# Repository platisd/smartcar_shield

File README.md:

# Smartcar shield

A versatile and easy to use vehicle platform for hobby-grade projects

* [Description](#description)
* [Hardware](#hardware)
  * [Platform](#platform)
  * [Shield](#shield)
  * [Emulator](#emulator)
* [Software](#software)
* [Reference platforms](#reference-platforms)
  * [Smartcar platform (default setup)](#smartcar-platform-default-setup)
  * [Smartcar shield](#smartcar-shield-1)
  * [Supported sensors](#supported-sensors)
* [How to get started](#how-to-get-started)
* [Dependencies](#dependencies)
* [Project documentation](#project-documentation)
* [License](#license)

## Description
This repository, includes everything necessary to set up a Smartcar platform.
The Smartcar, is a vehicular educational platform, which enables the user to develop
various robotic applications in an affordable, pedagogic and easy way. It is intended
for persons with basic programming knowledge and little to no experience of electronics,
mechanics or robotics. More experienced users, should also find this approach convenient,
due to its open source nature, high level API and object oriented design.

## Hardware
Despite the software being hardware-agnostic, historically, development has been based on specific
hardware. Initially, the **Smartcar shield** was used on top of an Arduino, using cheap car kits.
This setup will be referred to as `shield` or `v1`.

Since the winter of 2019, a new platform was developed from scratch, using the WiFi and Bluetooth
enabled ESP32 as the vehicle's "brain". This setup will be referred to as `platform` or `v2` and
will be considered the default one from now on. It offers greater robustness and many more
possibilities, as it offers out-of-the-box connectivity.

### Platform

The Smartcar platform is a complete hardware solution for your hobby-grade, connected vehicle project.
It is comprised of the chassis, made out of printed circuit boards, stacked on each other and an
ESP32 development board that drives the motors, controls the sensors and communicates with the
world via WiFi and Bluetooth.

There are 4 motors with directional odometers which enable not only to determine how much the
wheels have moved but also the direction they spin. It is equipped with a GY-50 gyroscope module
(based on the L3G4200D sensor) to provide heading information and sockets to optionally connect
4 `VL45L0X` LIDAR sensors to provide distance measurements. It is powered up by 8 AA batteries
and you can find the boards' source files in [extras/eagle/smartcar_platform](/extras/eagle/smartcar_shield).

### Shield

The Smartcar shield is an open hardware PCB, that is effortlessly stacked on top of an Arduino. It
includes an L293D H-bridge chip, that drives the motors, screw terminals to connect the motors
and a battery to them and a GY-50 gyroscope module (based on the L3G4200D sensor).
In [extras/eagle/smartcar_shield](/extras/eagle/smartcar_shield) you can find the
design files for the board, in a modifiable form, using free software. There are
also the options, to order it as-is, from either USA or China based manufacturers.

The Smartcar shield, facilitates efficient cable management, helps to preserve space
and is as small as possible, in order to keep the manufacturing price low. Additionally,
the components necessary to assemble it, are widely available over the Internet. Furthermore,
you can find 2D CAD drawings of the Smartcar chassis in various formats, at
[/extras/cad/2D](extras/cad/2D) which you can freely use in order to fabricate your own,
e.g. with a milling machine or a laser cutter.

### Emulator

[SMCE](https://github.com/ItJustWorksTM/smce-gd/) is the digital twin of the Smartcar platform
along with a cool and customisable 3D world for your rover to roam in.<br>
The core concept is that you write Arduino code that runs on both the real hardware as well as
the virtual environment.
This way, the need to have exclusive and frequent access to the car can be either alleviated
or drastically decreased.
The emulator allows limiting the unavoidable engagement with the physical car, to the point a
team of developers may develop their features on the emulator and only access the real hardware
to verify them.

## Software
The software, is the Smartcar shield Arduino library. It sports a high level API, meant to
enable its users to perform tasks easily with relatively few lines of code. It intends to
hide implementation details or low level hardware operations. The library, handles
the various components (i.e. the vehicle and the various sensors) as objects, therefore
enabling trivial control over the car's functions. The various operations exposed by the API,
are thoroughly explained in [API Documentation](https://platisd.github.io/smartcar_shield/).
You can find examples on how to use the library, in [/examples](/examples).

The library is versatile and is independent from the shield or specific hardware.
Particularly, its most important feature is that it supports multiple ways of steering and
throttling with different types of motors. Moreover, it is possible to steer the vehicle by
rotating the wheels on each side at a different speed, like a tank as well as by using a
servo motor. Another option is to use a brushed DC motor for steering, a setup that is very
common in cheap RC cars. Additionally, apart of the default brushed DC motors that are
connected to the Smartcar shield, you can also use an electronic speed controller (ESC)
in order to drive (throttle) the vehicle, using the very same library.

If the Smartcar shield library is installed through the Library Manager of Arduino IDE, as
recommended, the user will receive a notification in their IDE, when new versions are released
making updates particularly easy, without the need to use GitHub or git.

## Reference platforms

### Smartcar platform (default setup)

* 1 x [Modules board (rev.2)](https://www.pcbway.com/project/shareproject/Smartcar___Modules_board_rev_2.html)
* 1 x [Motor board (rev. 0)](https://www.pcbway.com/project/shareproject/Smartcar___Motors_board.html)
* 4 x [Brushed motors](https://www.aliexpress.com/item/32872592243.html) (530rpm @ 12V)
* 2 x [TXS0108E TTL level shifters](https://www.aliexpress.com/item/32472491036.html)
* 1 x DOIT ESP32 devkit v1 (30 GPIO pins)
* 1 x [TB6612FNG dual motor driver (Sparkfun)](https://www.sparkfun.com/products/14451)
* 4 x M6 (30mm) screws
* 4 x M6 nuts
* 16 x M3 (10mm) screws
* 16 x M3 nuts
* 2 x [HSP 02052 Front Bumper](https://www.aliexpress.com/item/32753903115.html)
* 10 x 6pin 2.54 pitch female pin headers
* 2 x 15pin 2.54 pitch female pin headers
* 1 x GY-50 gyroscope
* 4 x [8pin 2.54 pitch long male pin headers](https://www.aliexpress.com/item/32911455899.html) (30mm long)
* 4 x 8pin 2.54 pitch female pin headers
* 3 x 10KOhm resistors
* 8 x [AA battery holders](https://www.electrokit.com/produkt/batterihallare-1xaa-pcb/)
* 1 x [DD40AJSA adjustable buck converter](https://www.aliexpress.com/item/32816584868.html)
* 1 x [SPDT switch](https://www.tme.eu/en/details/5ms1s102am2qe/slide-switches/)
* 4 x [VL45L0x ToF distance sensors](https://www.aliexpress.com/item/32828144370.html) (optional)
  * 4 x 4pin 2.54 angled headers to mount the sensors vertically

### Smartcar shield

 * Smartcar chassis
 * [Smartcar shield PCB](extras/eagle/smartcar_shield)
 * L293D H-bridge
 * GY-50 gyroscope module
 * Two odometers (speed encoders) ([[1]](http://www.aliexpress.com/item/5pcs-IR-Infrared-Slotted-Optical-Speed-Measuring-Sensor-Optocoupler-Module-For-Motor-Test-For-Arduino-PIC/32465670452.html)
 and [[2]](http://www.aliexpress.com/item/HC-020K-Double-Speed-Measuring-Sensor-Module-with-Photoelectric-Encoders-Kit-top/32453020060.html)
 will suit commercially available chassis.
 [[3]](http://www.aliexpress.com/item/Correlation-photoelectric-sensor-lot-Infrared-correlation-count-sensor-module/2038553959.html)
 require some slight modifications)
 * Male & female pin headers (optionally get stackable Arduino headers too)
 * Five 2-pin screw terminals
 * Pin jumper
 * DIP16 socket
 * 0.1uF capacitors (2)
 * 100uF capacitor
 * 9V or 12V battery pack (do not use a single 9V battery)

### Supported sensors
 * Distance sensors
    * Ultrasonic
      * HC-SR04
      * SRF08
    * Infrared
      * SHARP GP2D120
      * SHARP GP2Y0A02
      * SHARP GP2Y0A21
 * Gyroscopes
   * GY-50 (L3G4200D)
 * Odometers
   * Directional (4+ pins)
   * Non-directional (3-pins)

## How to get started
 * Assemble the vehicle
 * [Install the library](https://www.ardu-badge.com/Smartcar%20shield)
 * [Connect the motors appropriately](examples/Car/shieldMotorsTest/shieldMotorsTest.ino) (if using the shield)
 * [Getting started with the Smartcar Platform](https://www.hackster.io/platisd/getting-started-with-the-smartcar-platform-1648ad)

## Dependencies
All dependencies should be downloaded automatically by the Arduino IDE's library manager.

- [Wire library](http://arduino.cc/en/reference/Wire)
- [Servo library](https://www.arduino.cc/en/reference/servo)
- [ESP32Servo](https://github.com/madhephaestus/ESP32Servo)

## Project documentation
* [API Documentation](https://platisd.github.io/smartcar_shield/)
* [The Smartcar platform](http://plat.is/smartcar)
* [Wiki](https://github.com/platisd/smartcar_shield/wiki)
* [Turning software engineers into Makers](https://platis.solutions/blog/2016/06/17/turning-software-engineers-into-makers/)

## License
MIT

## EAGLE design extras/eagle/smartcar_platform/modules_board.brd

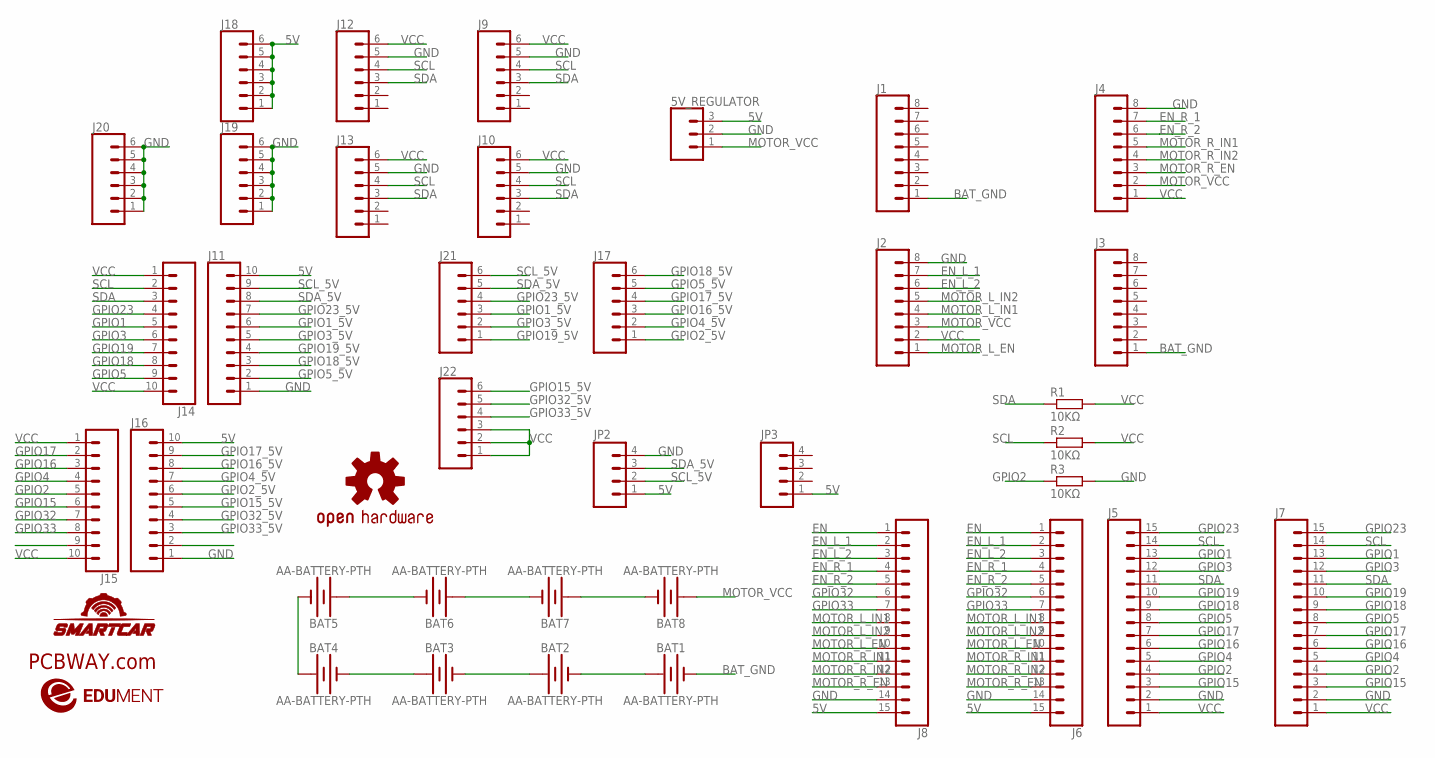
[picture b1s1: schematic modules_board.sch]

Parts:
5V_REGULATOR: CONN_03LOCK; 1X03_LOCK
BAT1, BAT2, BAT3, BAT4, BAT5, BAT6, BAT7, BAT8: AA-BATTERY-PTH; AA-PCB-BATTERY
J1, J2, J3, J4: CONN_08NO_SILK_FEMALE_PTH; 1X08_NO_SILK
J5, J6: CONN_15LOCK_LONGPADS; 1X15_LOCK_LONGPADS
J7, J8: CONN_15LOCK_NO_SILK; 1X15_LOCK_NO_SILK
J9, J10, J12, J13, J17, J18, J19, J20, J21, J22: CONN_06LOCK; 1X06_LOCK
J11, J14, J15, J16: CONN_10"; 1X10
JP2, JP3: M04NO_SILK_ALL_ROUND; 1X04_NO_SILK_ALL_ROUND
LOGO1: OSHW-LOGOL; OSHW-LOGO-L
R1, R2, R3: 10KΩ; 0207/12
SMRTCR1: SMARTCAR_LOGOMEDIUM; SMARTCAR_LOGO_MEDIUM
U$1: PCBWAY_LOGO
U$2: EDUMENT_LOGOLARGE; EDUMENT_LOGO_LARGE

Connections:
5V: 5V_REGULATOR.3, J6.15, J8.15, J11.10, J16.10, J18.1, J18.2, J18.3, J18.4, J18.5, J18.6, JP2.1, JP3.1
BAT_GND: BAT1.NEG (-), J1.1, J3.1
EN: J6.1, J8.1
EN_L_1: J2.7, J6.2, J8.2
EN_L_2: J2.6, J6.3, J8.3
EN_R_1: J4.7, J6.4, J8.4
EN_R_2: J4.6, J6.5, J8.5
GND: 5V_REGULATOR.2, J2.8, J4.8, J5.2, J6.14, J7.2, J8.14, J9.5, J10.5, J11.1, J12.5, J13.5, J16.1, J19.1, J19.2, J19.3, J19.4, J19.5, J19.6, J20.1, J20.2, J20.3, J20.4, J20.5, J20.6, JP2.4, R3.2
GPIO1: J5.13, J7.13, J14.5
GPIO1_5V: J11.6, J21.3
GPIO2: J5.4, J7.4, J15.5, R3.1
GPIO2_5V: J16.6, J17.1
GPIO3: J5.12, J7.12, J14.6
GPIO3_5V: J11.5, J21.2
GPIO4: J5.5, J7.5, J15.4
GPIO4_5V: J16.7, J17.2
GPIO5: J5.8, J7.8, J14.9
GPIO5_5V: J11.2, J17.5
GPIO15: J5.3, J7.3, J15.6
GPIO15_5V: J16.5, J22.6
GPIO16: J5.6, J7.6, J15.3
GPIO16_5V: J16.8, J17.3
GPIO17: J5.7, J7.7, J15.2
GPIO17_5V: J16.9, J17.4
GPIO18: J5.9, J7.9, J14.8
GPIO18_5V: J11.3, J17.6
GPIO19: J5.10, J7.10, J14.7
GPIO19_5V: J11.4, J21.1
GPIO23: J5.15, J7.15, J14.4
GPIO23_5V: J11.7, J21.4
GPIO32: J6.6, J8.6, J15.7
GPIO32_5V: J16.4, J22.5
GPIO33: J6.7, J8.7, J15.8
GPIO33_5V: J16.3, J22.4
MOTOR_L_EN: J2.1, J6.10, J8.10
MOTOR_L_IN1: J2.4, J6.8, J8.8
MOTOR_L_IN2: J2.5, J6.9, J8.9
MOTOR_R_EN: J4.3, J6.13, J8.13
MOTOR_R_IN1: J4.5, J6.11, J8.11
MOTOR_R_IN2: J4.4, J6.12, J8.12
MOTOR_VCC: 5V_REGULATOR.1, BAT8.POS (+), J2.3, J4.2
unnamed: BAT2.POS (+), BAT3.NEG (-)
unnamed: BAT1.POS (+), BAT2.NEG (-)
unnamed: BAT3.POS (+), BAT4.NEG (-)
unnamed: BAT4.POS (+), BAT5.NEG (-)
unnamed: BAT5.POS (+), BAT6.NEG (-)
unnamed: BAT6.POS (+), BAT7.NEG (-)
unnamed: BAT7.POS (+), BAT8.NEG (-)
SCL: J5.14, J7.14, J9.4, J10.4, J12.4, J13.4, J14.2, R2.1
SCL_5V: J11.9, J21.6, JP2.2
SDA: J5.11, J7.11, J9.3, J10.3, J12.3, J13.3, J14.3, R1.1
SDA_5V: J11.8, J21.5, JP2.3
VCC: J2.2, J4.1, J5.1, J7.1, J9.6, J10.6, J12.6, J13.6, J14.1, J14.10, J15.1, J15.10, J22.1, J22.2, J22.3, R1.2, R2.2

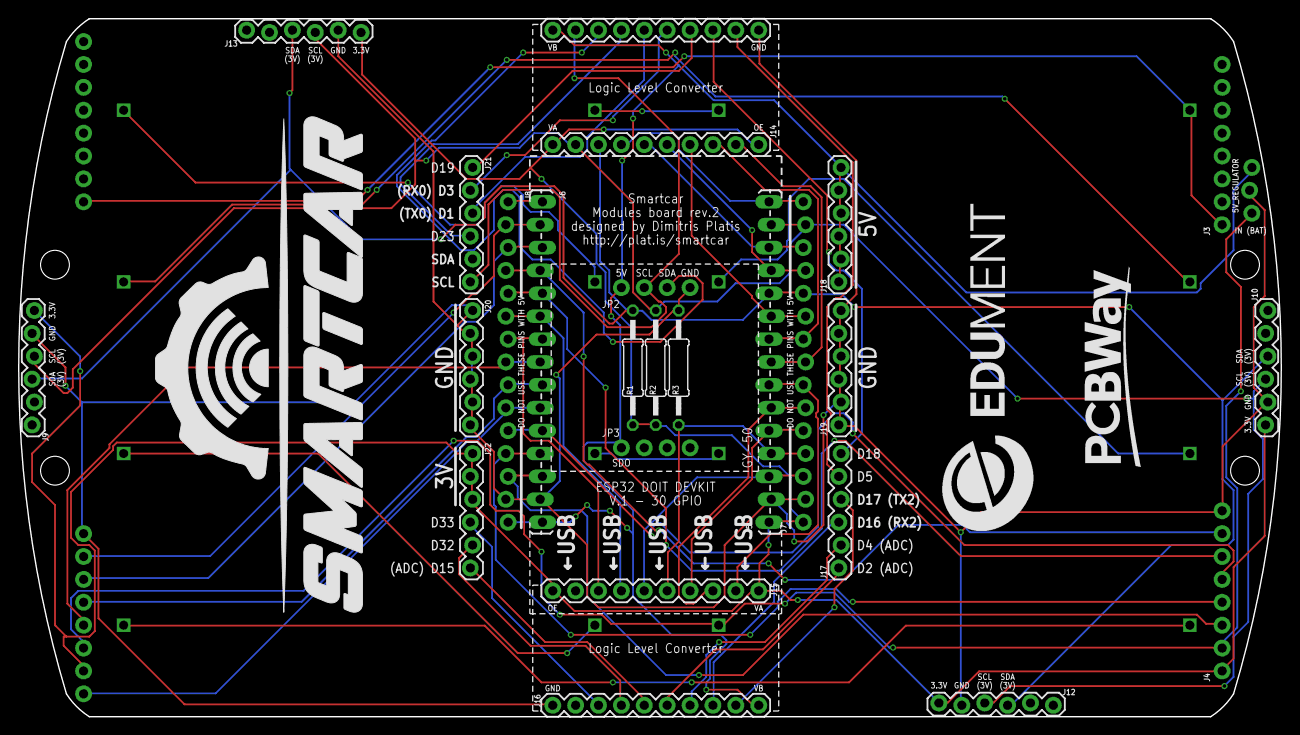
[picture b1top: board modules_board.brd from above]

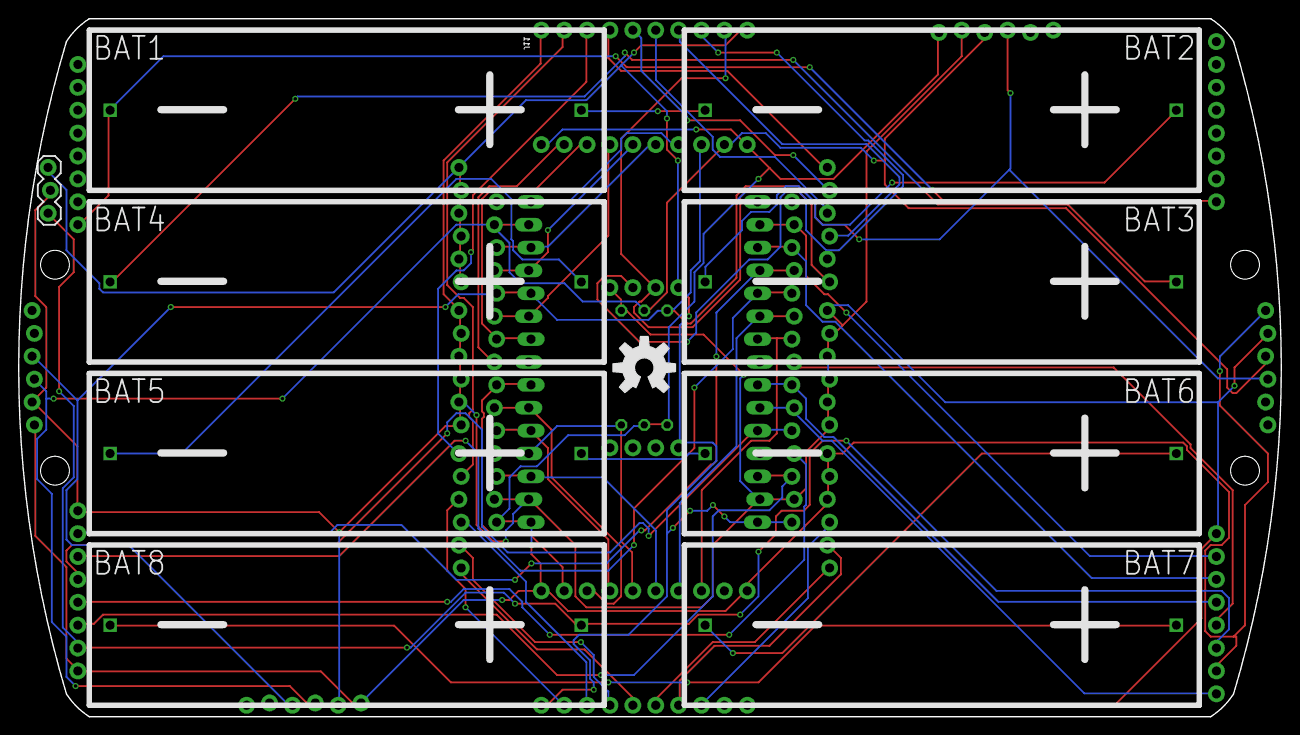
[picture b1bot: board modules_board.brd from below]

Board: 2 copper layers, 140.1 x 77.5 mm, 40 parts (10 on the bottom side), 53 nets.

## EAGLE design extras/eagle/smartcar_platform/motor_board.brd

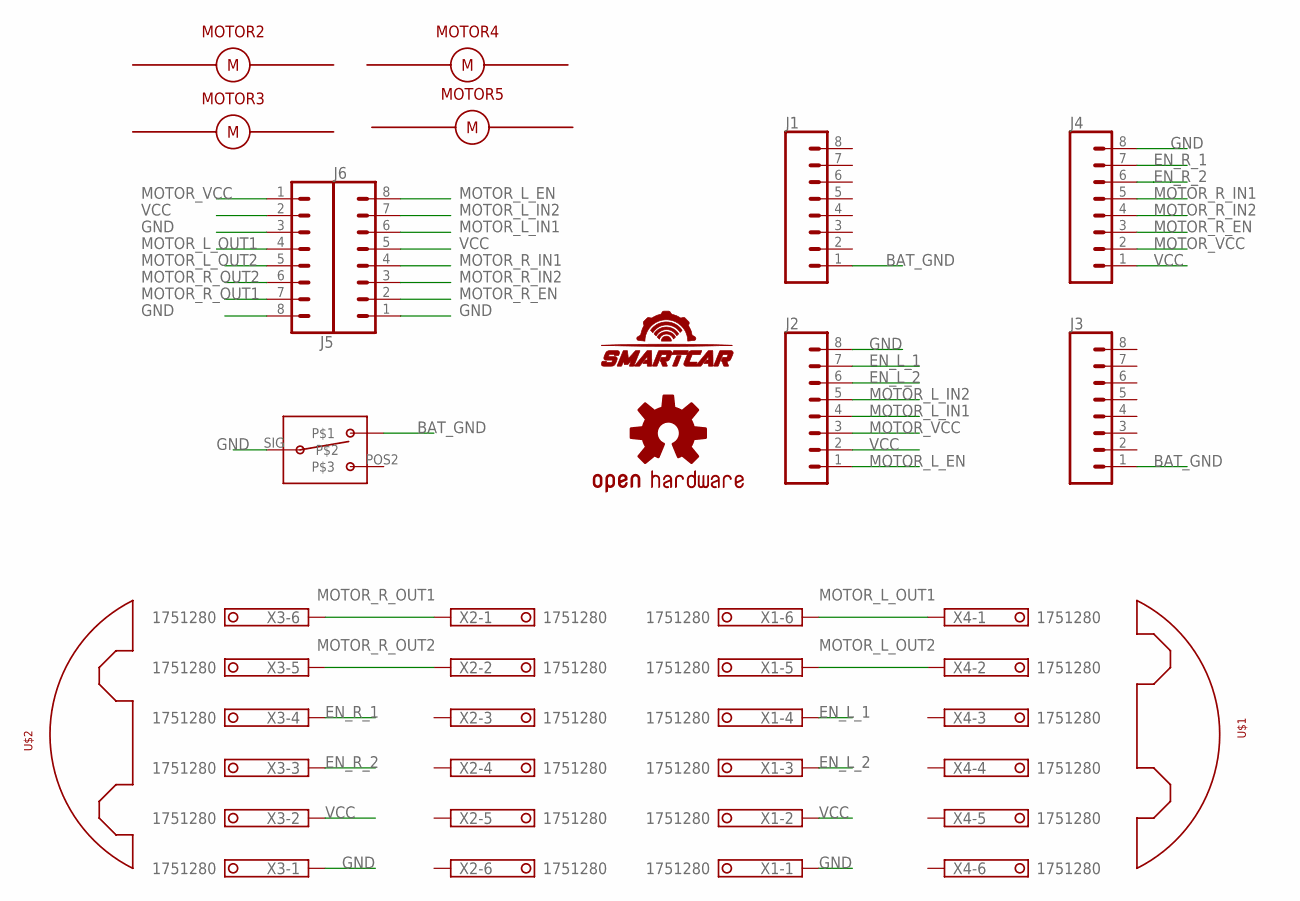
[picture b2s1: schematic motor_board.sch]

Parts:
J1, J2, J3, J4: CONN_08NO_SILK_FEMALE_PTH; 1X08_NO_SILK
J5, J6: CONN_08"; 1X08
LOGO1: OSHW-LOGOL; OSHW-LOGO-L
MOTOR2, MOTOR3, MOTOR4, MOTOR5: SMARTCAR_MOTOR; SMARTCAR_MOTOR_MOUNT_HOLES
SMRTCR1: SMARTCAR_LOGOMEDIUM; SMARTCAR_LOGO_MEDIUM
SW1: SPDT-HIGH-AMP-SWITCHPTH; SPDT-0.2-THICK-PINS
U$1, U$2: BUMPER_020522_SCREWS; BUMPER_2_SCREWS_NARROW
X1, X2, X3, X4: 1751280

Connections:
BAT_GND: J1.1, J3.1, SW1.POS1
EN_L_1: J2.7, X1.4
EN_L_2: J2.6, X1.3
EN_R_1: J4.7, X3.4
EN_R_2: J4.6, X3.3
GND: J2.8, J4.8, J5.3, J5.8, J6.1, SW1.SIG, X1.1, X3.1
MOTOR_L_EN: J2.1, J6.8
MOTOR_L_IN1: J2.4, J6.6
MOTOR_L_IN2: J2.5, J6.7
MOTOR_L_OUT1: J5.4, X1.6, X4.1
MOTOR_L_OUT2: J5.5, X1.5, X4.2
MOTOR_R_EN: J4.3, J6.2
MOTOR_R_IN1: J4.5, J6.4
MOTOR_R_IN2: J4.4, J6.3
MOTOR_R_OUT1: J5.7, X2.1, X3.6
MOTOR_R_OUT2: J5.6, X2.2, X3.5
MOTOR_VCC: J2.3, J4.2, J5.1
VCC: J2.2, J4.1, J5.2, J6.5, X1.2, X3.2

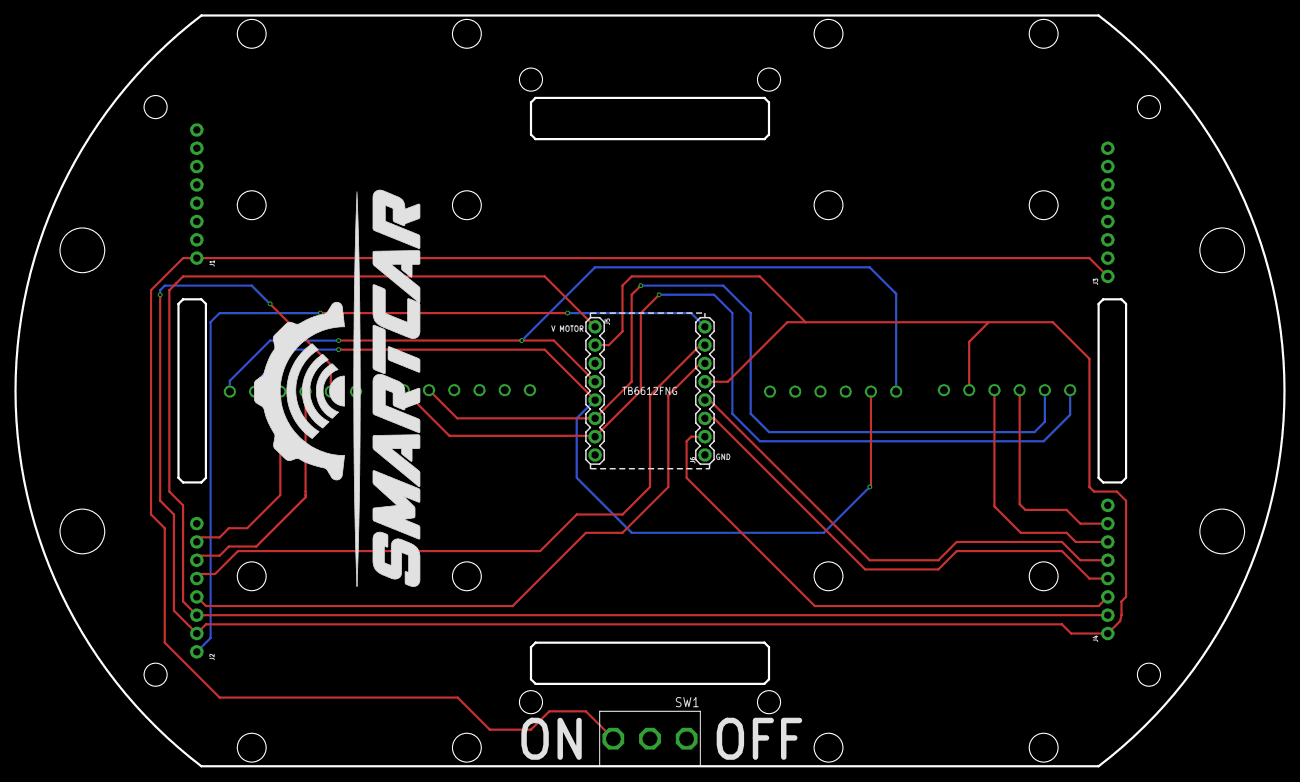
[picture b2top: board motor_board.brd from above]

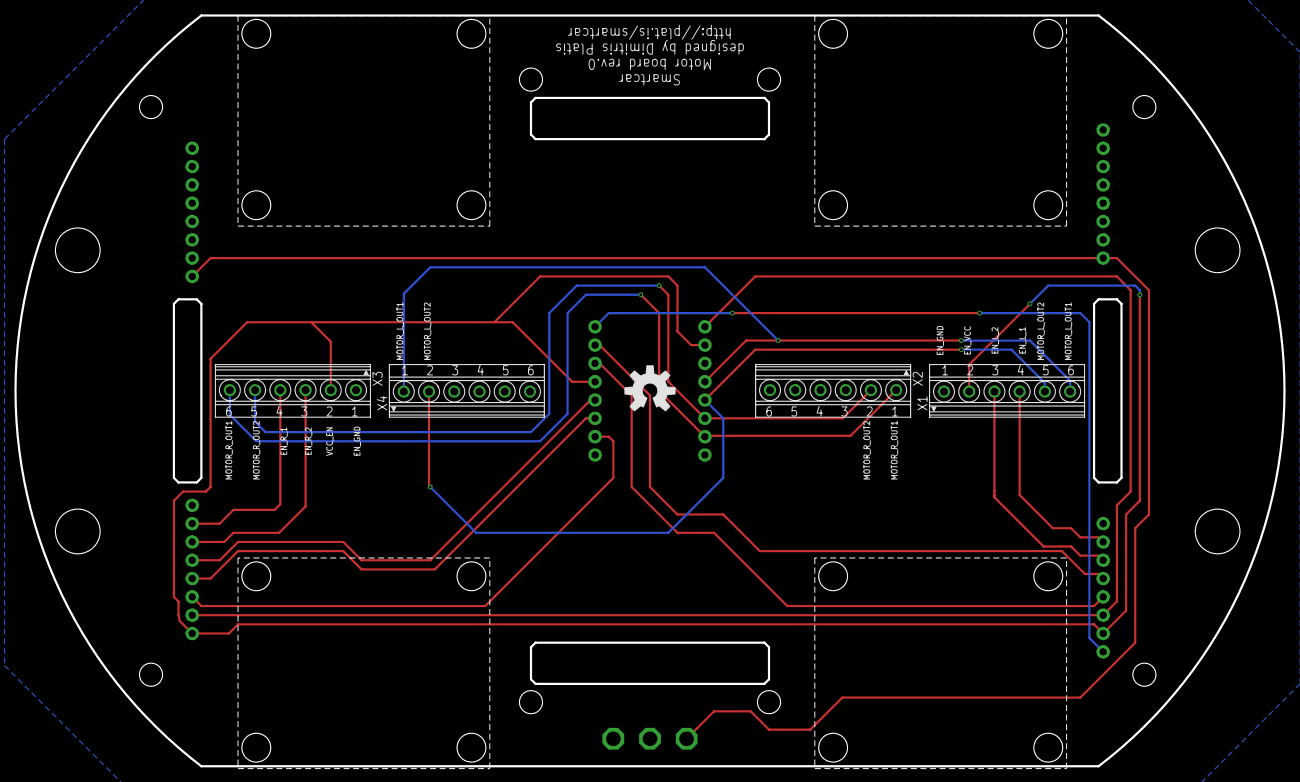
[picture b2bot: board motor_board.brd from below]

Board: 2 copper layers, 176.0 x 104.1 mm, 19 parts (9 on the bottom side), 18 nets.

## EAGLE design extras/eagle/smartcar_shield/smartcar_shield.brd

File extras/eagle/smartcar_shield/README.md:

# Smartcar shield CAD files

### Description
Here you can find the files necessary in order to edit or manufacture the Smartcar shield PCB. The files can be opened using CAD software, such as Eagle PCB that is free for personal use and KiCad, which is open source. The .sch file includes the logical schematic of the circuit, that is how the various components are connected to each other and the .brd file illustrates how they will be printed on the actual board.

All components that are needed for the board, are through-hole, for easy soldering. Finally, feel free to edit or redistribute the shield. Pull requests are always welcome.

### Order a PCB
If you do not want to bother with CAD softwareand just want to buy the PCBs for the shield, I have uploaded the necessary files in two popular services, [OSH-Park](https://oshpark.com/) (USA) and [PCBWay](https://www.pcbway.com/) (China), so they can be purchased with a few clicks.

**Note: I am not affiliated with either of these services, however I do receive a 10% commission in coupons from [PCBway](https://www.pcbway.com/) when you order the boards from them.**

* [PCBWay](https://www.pcbway.com/project/shareproject/SmartCar_Shield_rev__2.html) (rev. 2)
* [OSH-Park](https://oshpark.com/shared_projects/pCO3kBPB) (rev. 2)

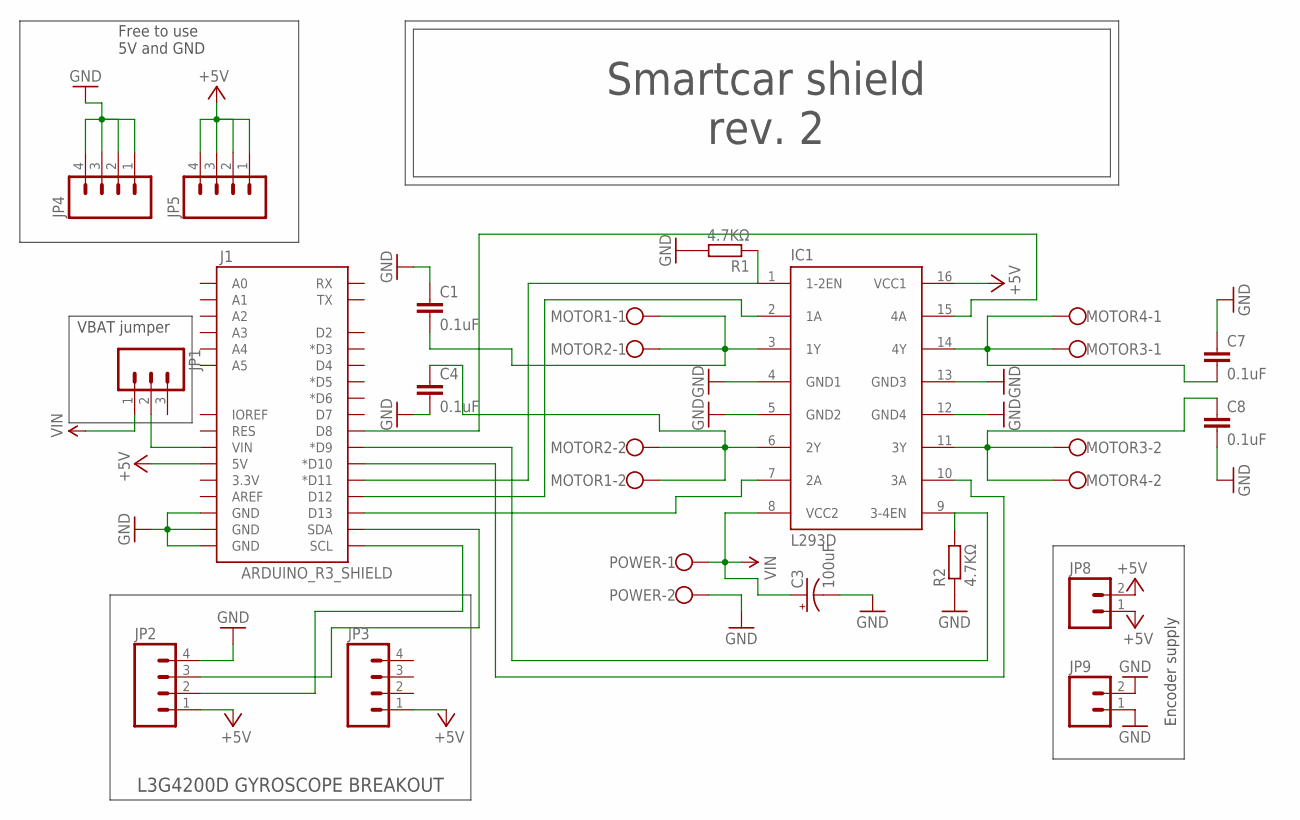
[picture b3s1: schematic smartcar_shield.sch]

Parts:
C1, C4, C7, C8: 0.1uF; CAP-PTH-SMALL-KIT
C3: 100uF; CPOL-RADIAL-10UF-25V
IC1: L293D; DIL16
J1: ARDUINO_R3_SHIELD; UNO_R3_SHIELD
JP1: M03PTH; 1X03
JP2, JP3, JP4, JP5: M04NO_SILK_ALL_ROUND; 1X04_NO_SILK_ALL_ROUND
JP8, JP9: M021X02_NO_SILK; 1X02_NO_SILK
MOTOR1, MOTOR2, MOTOR3, MOTOR4: W237-102
POWER: W237-102
R1, R2: 4.7KΩ; 0207/10

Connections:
12V: C3.1 (+), IC1.8 (VCC2), JP1.1, POWER.1
+5V: IC1.16 (VCC1), J1.5V, JP2.1, JP3.1, JP5.1, JP5.2, JP5.3, JP5.4, JP8.1, JP8.2
ENABLE1: IC1.1 (1-2EN), J1.D11 (*D11), R1.1
ENABLE2: IC1.9 (3-4EN), J1.D9 (*D9), R2.2
GND: C1.1, C3.2 (-), C4.2, C7.1, C8.2, IC1.4 (GND1), IC1.5 (GND2), IC1.12 (GND4), IC1.13 (GND3), J1.GND@0 (GND), J1.GND@1 (GND), J1.GND@2 (GND), JP2.4, JP4.1, JP4.2, JP4.3, JP4.4, JP9.1, JP9.2, POWER.2, R1.2, R2.1
MOTORA-1: IC1.2 (1A), J1.D12
MOTORA-2: IC1.7 (2A), J1.D13
MOTORA-OUT1: C1.2, IC1.3 (1Y), MOTOR1.1, MOTOR2.1
MOTORA-OUT2: C4.1, IC1.6 (2Y), MOTOR1.2, MOTOR2.2
MOTORB-1: IC1.15 (4A), J1.D8
MOTORB-2: IC1.10 (3A), J1.D10 (*D10)
MOTORB-OUT1: C7.2, IC1.14 (4Y), MOTOR3.1, MOTOR4.1
MOTORB-OUT2: C8.1, IC1.11 (3Y), MOTOR3.2, MOTOR4.2
unnamed: J1.SDA, JP2.3
SCL: J1.SCL, JP2.2
VIN: J1.VIN, JP1.2

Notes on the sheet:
Encoder supply
Free to use 5V and GND
VBAT jumper
Smartcar shield rev. 2
L3G4200D GYROSCOPE BREAKOUT

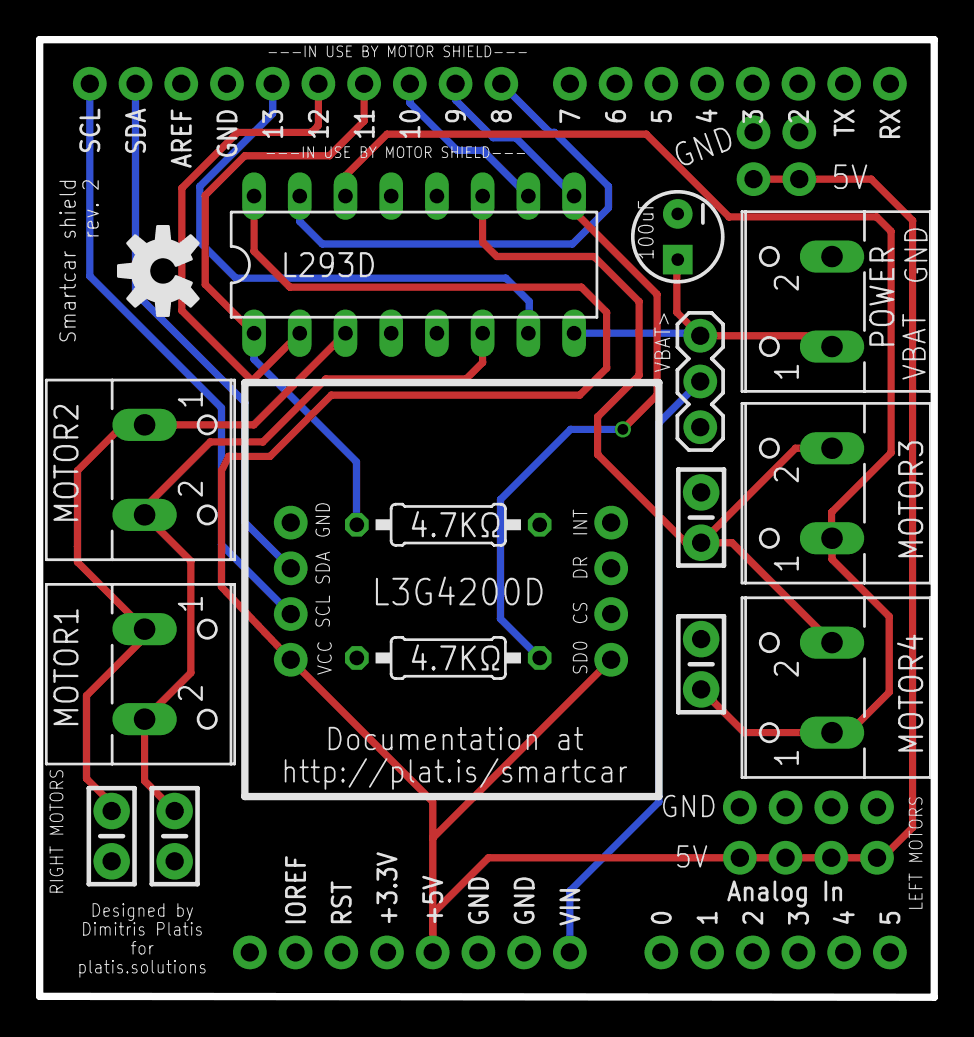
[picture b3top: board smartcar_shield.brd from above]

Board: 2 copper layers, 49.7 x 53.2 mm, 22 parts (0 on the bottom side), 16 nets.

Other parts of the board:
U$1: OSHW-LOGO-M

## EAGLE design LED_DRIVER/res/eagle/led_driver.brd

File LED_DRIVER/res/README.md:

# LED DRIVER
The LED driver board, is based on an ATTiny85 microcontroller and is used in order to drive the LEDs that can be found on the vehicle and particularly the direction indicators. In the [/res](res) folder, you can find the board's schema, how it looks like and also the Eagle files if you want to modify it or fabricate it yourself. Moreover, if you want just to reproduce the board, you can order it from [OSH Park](https://oshpark.com/shared_projects/Hk4up6hJ).

### Materials used
* 6 screw terminals ([Sparkfun](https://www.sparkfun.com/products/8432))
* 4 NPN transistors (BC547)
* 4 1.5KΩ resistors
* 1 ATtiny85-20PU microcontroller
* 1 socket 8 DIP (optional but strongly recommended)

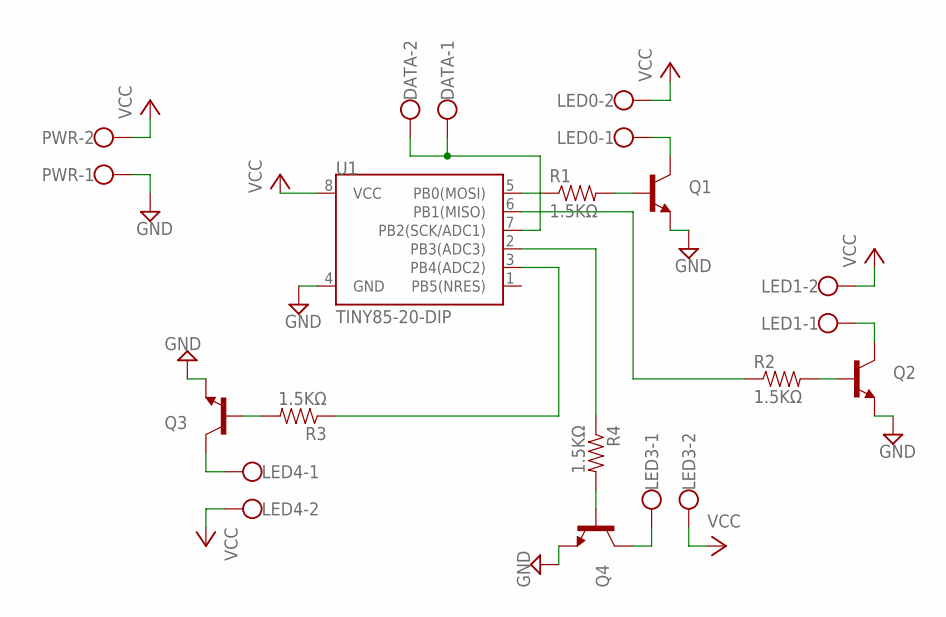
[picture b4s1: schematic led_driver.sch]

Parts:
DATA: W237-102
LED0, LED1, LED3, LED4: W237-102
PWR: W237-102
Q1, Q2, Q3, Q4: TRANSISTOR_NPNBC547; TO-92-AMMO
R1, R2, R4: 1.5ΚΩ; AXIAL-0.3
R3: 1.5KΩ; AXIAL-0.3
U1: TINY85-20-DIP; DIP08

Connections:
DATA-IN: DATA.1, DATA.2, U1.7 (PB2(SCK/ADC1))
GND: PWR.1, Q1.3 (E), Q2.3 (E), Q3.3 (E), Q4.3 (E), U1.4 (GND)
LED0: R1.P$1 (1), U1.5 (PB0(MOSI))
LED0-GND: LED0.1, Q1.1 (C)
LED1: R2.P$1 (1), U1.6 (PB1(MISO))
LED1-GND: LED1.1, Q2.1 (C)
LED3: R4.P$1 (1), U1.2 (PB3(ADC3))
LED3-GND: LED3.1, Q4.1 (C)
LED4: R3.P$1 (1), U1.3 (PB4(ADC2))
LED4-GND: LED4.1, Q3.1 (C)
unnamed: Q1.2 (B), R1.P$2 (2)
unnamed: Q2.2 (B), R2.P$2 (2)
unnamed: Q3.2 (B), R3.P$2 (2)
unnamed: Q4.2 (B), R4.P$2 (2)
VCC: LED0.2, LED1.2, LED3.2, LED4.2, PWR.2, U1.8 (VCC)

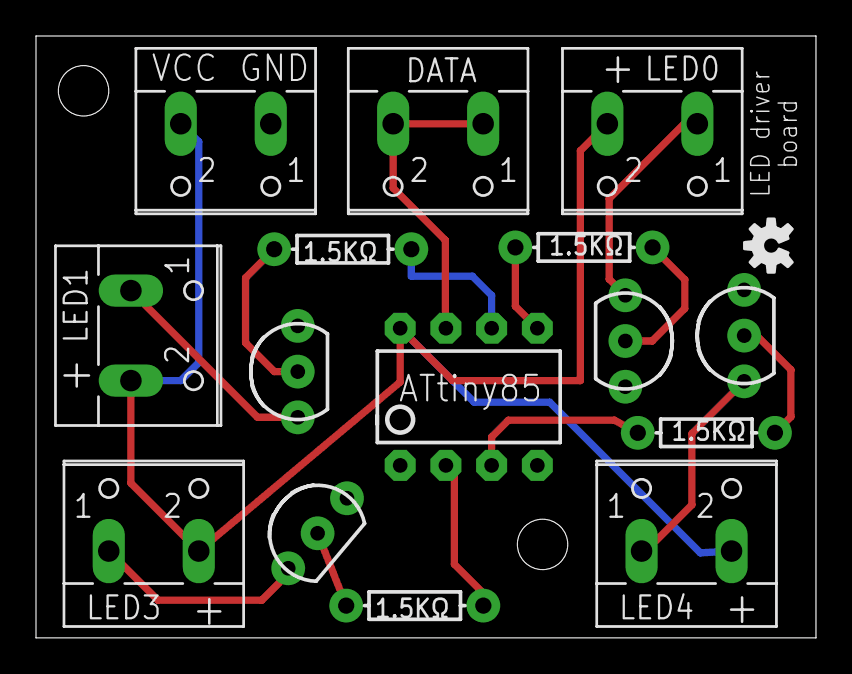
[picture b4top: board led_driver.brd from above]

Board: 2 copper layers, 43.3 x 33.4 mm, 16 parts (0 on the bottom side), 15 nets.

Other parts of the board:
U$1: OSHW-LOGO-S

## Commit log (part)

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2017-01-16 user to set the state the direction pin should be in when going forward
2017-01-16 Bumping version
    And also setting the default go speed back to what it was
2017-01-16 Revert "decreasing the maximum allowed speed for safety reasons"
    This reverts commit 70319889b9c457c7b791982763eb85e9415bb38e.
2017-01-16 new getDirection and Car class constructor For odometers that can provide the direction of movement and a Car with two motors attached to arbitrary pins
2017-01-16 decreasing the maximum allowed speed for safety reasons
2018-04-07 Remove i2c blocking loop
    Related to platisd/AndroidCar#1
2018-04-07 Fix wording
2018-05-14 solved method detection issue with @archico
2018-05-14 fixed method recognition for disableCruiseControl co-authored-by: Ilja Pavlov <guspavloil@student.gu.se>
2018-05-22 Bump library version with runaway fix
2018-07-23 Add version 5 structure
    Includes:
    * Folder structure
    * Interfaces and header files
2018-07-24 Add initial test structure
2018-07-24 Cache gtest sources
2018-07-24 Add coverage reports
2018-07-26 Rename Steering to Control
    Since we will be having the Steering-Throttling concepts
    later on, it's best to decouple these to avoid confusion
2018-07-26 Add Arduino runtime implementation
2018-07-26 Define DistanceSensor interface
2018-07-29 Add map and constrain functions
2018-09-30 Migrate SRF08 sensor class
2018-10-01 Add tests for SRF08 sensor
2018-10-01 Refactor SR04 sensor class
2018-10-12 Refactor SR04 class
2018-10-13 Refactor SHARP IR sensors
2018-10-14 Add new Odometer implementation
    TODO: Fix missing unit tests
2018-10-21 Test the Odometer constructor
2018-10-27 Rename orientation to heading
    For better representation of the business domain
2018-10-28 Refactor GY50 sensor (ex Gyroscope)
2018-10-30 Rename motor to motors
    Naming should be consistent with that of sensors
2018-10-31 Add brushless motor
2018-11-02 Use templatized map function instead of the Arduino one
2018-11-02 Add ServoMotor
2018-11-03 Add Ackerman and Differential controls
2018-11-03 Add utility function for tests and coverage
2018-11-04 Remove unused functions from runtime interface
2018-11-04 Test for not attached SHARP sensors
2018-11-04 Test reset() function of Directional odometer
2018-11-04 Rename odometer package
2018-11-04 Move directly-controlled odometers in separate folder
2018-11-04 Update tests and code after odometer renaming
2018-11-04 Adjust tests to directionless odometer naming
2018-11-04 Make SHARP sensor pin a constructor argument
    This will eliminate misuse and simplify the code
2018-11-04 Force SRF08 address to be a constructor argument
2018-11-04 Rename initialized to attached so to maintain common terms
2018-11-04 Eliminate the need for the user to attach() the sensor
    All needed initialization will be done (if not already done)
    when probing the sensor.
2018-11-04 Move all source code out of include folder
    Since we are following the Arduino file structure
    having an include/ folder does not make much sense,
    especially since it contained source code as well.
2018-11-05 Enable individual motor control
    In some cases advanced users find it useful to be able
    to control each motor on the car individually.
2018-11-05 Do not set pin direction if attach failed
2018-11-06 Add HeadingCar
2018-11-07 Rename to providesDirection
2018-11-07 Add comparison for floats
2018-12-06 Add DistanceCar implementation
2018-12-06 Configure tests by defining only their executable name
2019-01-13 Fix typo
2019-01-15 Make Smartcar.h as the library's entrypoint
    * Remove old source code (used for reference during refactoring)
    * Remove commented out class declarations (used for reference during refactoring)
2019-01-16 Fix measurement timeout
    * Time that sound needs to make a roundtrip is not equal to time
    that is needed for the sensor to make a measurement. Therefore an
    update is necessary in order to be able to conduct measurements up
    to our specified maximum distance.
    * Measurements larger than the max distance return error.
2019-01-16 Enforce pulses per meter ratio as argument
    This is in order to decrease accidental misuse
2019-01-16 Update sensor examples according to version 5 API
2019-01-17 Add collaboration templates
2019-01-17 Update Car examples to new library API
    * Also add examples for the new Car child classes
2019-01-17 Update highlighted keywords
2019-01-18 Build library examples in Travis CI :metal:
2019-01-18 Remove CC license, release everything under MIT
2019-01-18 Add docs folder
2019-01-18 Deploy platisd/smartcar_shield to github.com/platisd/smartcar_shield.git:gh-pages
2019-01-18 Ignore files generated by CI
2019-01-18 Remove files from documentation branch
2019-01-19 Ignore any downloaded Arduino IDE version
2019-01-19 Update documentation with links to doxygen pages
2019-01-19 Update testing contribution guidelines
2019-01-19 Treat all compiler warnings as errors
    * Fix warnings so the tests can compile
2019-01-19 Run static code analysis in CI
2019-01-20 Turn of Jekyll so files starting with underscore are visible
    Workaround for files starting with underscore not being displayed
    Source: https://help.github.com/articles/files-that-start-with-an-underscore-are-missing/
2019-01-20 Rename SR04 example
2019-01-20 Expect attach calls
    Currently, these two expectations are there only for the coverage.
    Unfortunately, due to how Arduino handles external interrupt
    registrations (and particularly the lack of an std::function
    implementation or the ability to attach interrupts before setup)
    we need the user to call attach manually, outside the library.
    Ideally, attach should not even be needed to be called
2019-01-21 Update docs main page
2019-01-22 Refactor to build library on esp8266
    Seems like esp8266 uses a rather different g++ so some syntax was
    not compatible with it. Interesting to know that compiling in
    Arduino IDE for AVR seems to be use a more modern configuration... :confused:
2019-01-24 Instantiate the Arduino runtime default argument in main header
    This way we do not pollute our implementation with a seamingly
    needless instatiation.
    Additionally, we now define the macro to trigger the default
    injection of the runtime environment on the Smartcar.h header
    so to make things more transparent, as opposed to this happening
    inside a cmake file for tests.
2019-02-06 Use ArduBadge instructions on how-to install
2019-06-17 Add Better Code Hub configuration
2019-06-17 Remove duplicate code
    Fixes #13
2019-06-17 Remove duplicate code (#14)
    Fixes #13
2020-01-05 Specify library dependencies in library.properties
    Specifying the library dependencies in the depends field of library.properties causes the Arduino Library Manager (Arduino IDE 1.8.10 and newer) to offer to install any missing dependencies during in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
2020-01-05 Specify library dependencies in library.properties (#19)
    Specifying the library dependencies in the depends
    Field of library.properties causes the Arduino Library
    Manager (Arduino IDE 1.8.10 and newer) to offer to
    install any missing dependencies during installation
    of this library. "arduino-cli lib install" will automatically
    Install the dependencies (arduino-cli 0.7.0 and newer).
2020-02-10 Remove duplicate code from initializer list (#20)
    Fixes #17
2020-02-12 Simplify DirectionalOdometer constructor by assuming LOW as direction state
2020-02-12 Make runtime compatible with ESP8266
2020-02-12 Increase unit test robustness by specifying a random forward state value
2020-02-12 Update unit tests
2020-02-12 Pass all required resources to Odometer constructors
2020-02-12 Revert pulses counter to being a private variable
2020-02-12 Improve correctness and performance of directional odometers
2020-02-12 Remove submodules
    We are going to use the new IDE feature and
    declare them as dependencies there instead.
2020-02-12 Add dependencies for library manager
2020-02-12 Use std::function in Odometer::attach
2020-02-12 Remove error value return when Odometer not attached
    If an Odometer is not attached due to bad pin, then no good
    values will be received anyway and the user can check if this
    happened succesfully by calling the isAttached method.
2020-02-12 Improve coverage report utilities
2020-02-12 Update tests to cover new code branches
2020-02-12 Fix clang-tidy warnings and run it on CI
2020-02-12 Enable ubuntu-toolchain-r/test PPA on bionic Travis runner
2020-02-12 Remove unused variable
2020-02-12 Move static constants into anonymous namespace
2020-02-12 Brake more smoothly to avoid excess power pull
2020-02-13 Remove filter for opposite pulses
    Things seem to be working fine for the time being...
2020-02-13 Update examples to use helper BrushedMotorPins wrapper
2020-02-14 Update examples with modified namespace
2020-02-14 Fix broken examples due to misformatting
2020-02-14 Update documentation for new platform
2020-02-16 Add utility variables for odometer pin on v2 platform and use them in examples
2020-02-17 Remove unnecessary parts of the URL
2020-03-29 Specify chip on TTL level shifters
2020-05-28 Add compiler flags and fix warnings
2020-06-07 Fix failing GoogleTest compilation
    It seems like we are fetching a new GoogleTest version
    that does not play nicely with all the flags we have.
    Let's remove that warning when compiling the GoogleTest
    library.
2020-06-07 Update examples for new API
2020-06-22 Set motors to idle when speed is 0
    This will allow the motors to handle cases where no PWM pin is
    specified and the motor driver's enable pin is directly wired to
    VCC
2020-11-07 Add test job
2020-11-07 Deploying to gh-pages from @ 2126da3aa251c4ca938324f68cb8cabc9ded732a 🚀
2020-11-07 Deploy doxygen documentation with Google Actions
2020-11-07 Update CI badges
2020-11-07 Make CI job naming consistent
2020-11-08 Verify commit messages follow best practices
2020-11-09 Use proper action for building examples on CI
2020-11-15 Add stricter clang-tidy configuration
2020-11-15 Undo some fixes due to lack of support on 8bit AVR
2020-11-16 Replace math.h header with C++ equivalent
2021-02-03 Deploying to gh-pages from @ 240d2da778c3ccca7518ba09ec6f4f8c3abbace1 🚀
2021-02-07 Fix wrong order of arguments in MockServo
2021-02-13 Check for duplicate code
2021-02-13 Trigger job on pull request comment
2021-02-13 Try more directories
2021-02-16 Remove github token
2021-04-09 Deploying to gh-pages from @ 1f0365590fd4bc27ec235c9d64369b146c99dac2 🚀
2021-04-09 Trigger CI on external pull requests (#41)
2021-04-11 Revert "Fix clang-tidy warnings"
    This reverts commit f0278e4afaa88ce7a02fb801db305842b6d030ba.
2021-04-16 Fix doxygen comments
2021-04-16 Deploying to gh-pages from @ 5c0f8cbcb1d947f36bef9ec63d06386c1c761809 🚀
2021-04-24 Fix action
2021-04-24 Try clang-tidy-8 again
2021-04-24 Update action URL
2021-04-24 Add missing header
2021-04-24 Run clang-tidy action only for clang builds
    No need to comment twice
2021-05-01 Fix ESP32 power supply line to 5V
    ESP32 was powered on via its VIN pin which based
    on the specs of the ESP32 DOIT devkit is supposed
    to handle up to 12V.
    This isn't actually the case and anything above 6V
    makes the regulator on the board overheat.
    Note that the 5V is actually the voltage coming from
2021-05-05 Add ON/OFF switch to components list
2021-09-16 Fix failing gmock compilation
2021-09-17 Use CMake tests project as base path
2021-09-18 Exclude gtest boilerplate from default build
2021-09-18 Simplify CMake coverage integration
2022-01-22 1 this should not work
2022-03-19 Use brace initialization for Odometer constructors
    Let's use brace initialization for Odometer constructors not
    so much because it's more idiomatic, but mostly due to problems
    when compiling with SMCE on Windows
2022-03-19 Fix broken test configuration
    googletest master seems to be different nowdays
    let's lock on to an old release
2022-04-25 BLop
2022-09-12 Deploying to gh-pages from @ 0631781e3d6d20a222c86b7dd9481b349caa4043 🚀
2022-10-04 Create License
2023-03-11 Add DualMotors example sketch
2023-03-13 Autofill PR description with OpenAI

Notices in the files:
parts and their libraries:
SparkFun-DigitalIC: Licensing: Creative Commons ShareAlike 4.0 International - https://creativecommons.org/licenses/by-sa/4.0
